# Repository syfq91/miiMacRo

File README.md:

# miiMacRo

TODO
- check clashes between rotary encoder & pro micro

Parts
https://www.aliexpress.com/item/33001477248.html?spm=a2g0o.productlist.0.0.1fc069f9uBTgRQ&algo_pvid=fa91f944-a301-4584-9e83-a4903b927c4c&algo_expid=fa91f944-a301-4584-9e83-a4903b927c4c-3&btsid=0b0a555816106226090074678e93b1&ws_ab_test=searchweb0_0,searchweb201602_,searchweb201603_

https://www.aliexpress.com/item/32625448150.html?spm=a2g0o.productlist.0.0.1fc069f9uBTgRQ&algo_pvid=fa91f944-a301-4584-9e83-a4903b927c4c&algo_expid=fa91f944-a301-4584-9e83-a4903b927c4c-5&btsid=0b0a555816106226090074678e93b1&ws_ab_test=searchweb0_0,searchweb201602_,searchweb201603_

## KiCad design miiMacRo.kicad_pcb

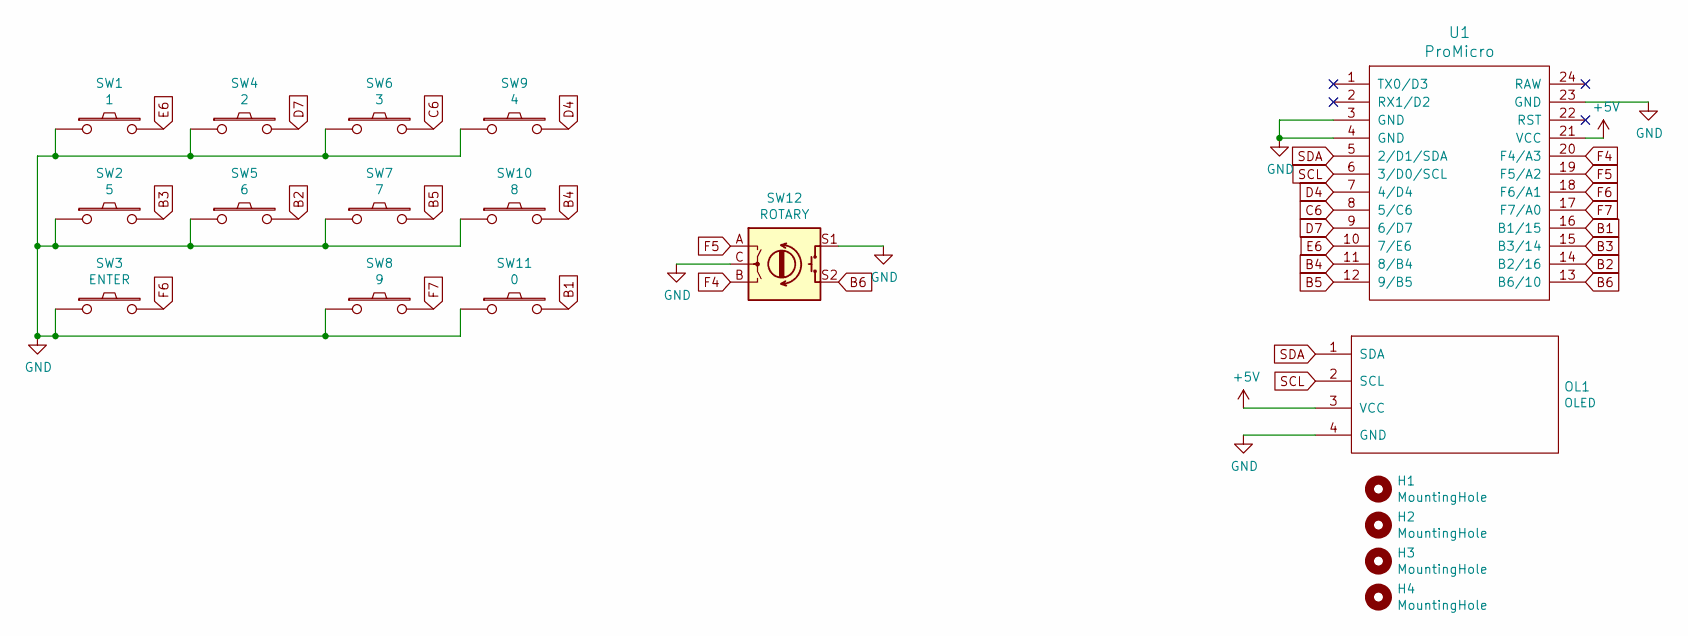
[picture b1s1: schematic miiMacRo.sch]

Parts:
H1, H2, H3, H4: MountingHole; M2_Hole_TH
OL1: OLED; OLED_v2
SW1: 1; MXOnly-1U-NoLED
SW2: 5; MXOnly-1U-NoLED
SW3: ENTER; MXOnly-2U-ReversedStabilizers-NoLED
SW4: 2; MXOnly-1U-NoLED
SW5: 6; MXOnly-1U-NoLED
SW6: 3; MXOnly-1U-NoLED
SW7: 7; MXOnly-1U-NoLED
SW8: 9; MXOnly-1U-NoLED
SW9: 4; MXOnly-1U-NoLED
SW10: 8; MXOnly-1U-NoLED
SW11: 0; MXOnly-1U-NoLED
SW12: ROTARY; RotaryEncoder_Alps_EC11E-Switch_Vertical_H20mm
U1: ProMicro; ArduinoProMicro-ZigZag

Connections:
+5V: OL1.3 (VCC), U1.21 (VCC)
B1: SW11.2, U1.16 (B1/15)
B2: SW5.2, U1.14 (B2/16)
B3: SW2.2, U1.15 (B3/14)
B4: SW10.2, U1.11 (8/B4)
B5: SW7.2, U1.12 (9/B5)
B6: SW12.S2, U1.13 (B6/10)
C6: SW6.2, U1.8 (5/C6)
D4: SW9.2, U1.7 (4/D4)
D7: SW4.2, U1.9 (6/D7)
E6: SW1.2, U1.10 (7/E6)
F4: SW12.B, U1.20 (F4/A3)
F5: SW12.A, U1.19 (F5/A2)
F6: SW3.2, U1.18 (F6/A1)
F7: SW8.2, U1.17 (F7/A0)
GND: OL1.4 (GND), SW1.1, SW2.1, SW3.1, SW4.1, SW5.1, SW6.1, SW7.1, SW8.1, SW9.1, SW10.1, SW11.1, SW12.C, SW12.S1, U1.3 (GND), U1.4 (GND), U1.23 (GND)
SCL: OL1.2 (SCL), U1.6 (3/D0/SCL)
SDA: OL1.1 (SDA), U1.5 (2/D1/SDA)

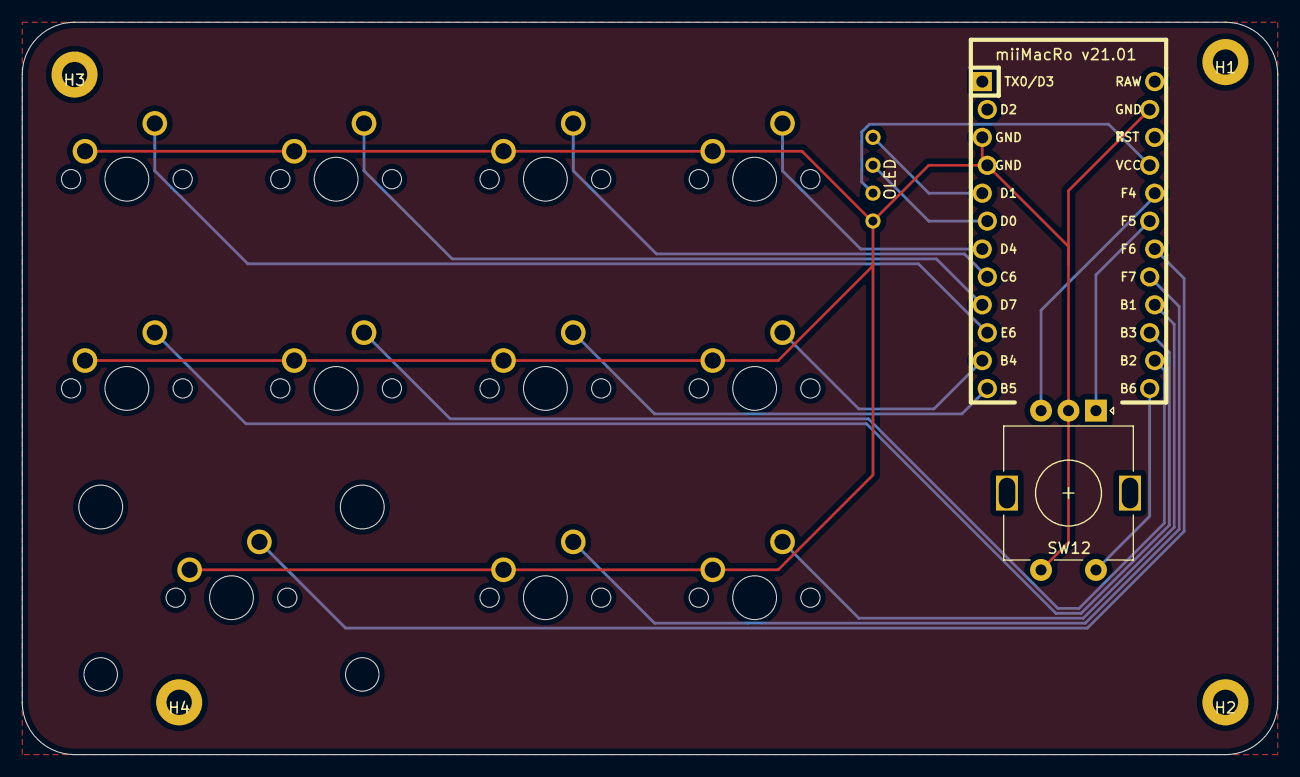
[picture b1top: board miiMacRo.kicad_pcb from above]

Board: 2 copper layers, 114.3 x 66.7 mm, 18 parts (0 on the bottom side), 18 nets.

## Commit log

2021-01-14 kicad setup
2021-01-14 first pcb design
2021-01-14 first complete pcb
